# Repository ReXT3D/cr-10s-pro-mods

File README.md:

# Creality CR-10S Pro hardware mods

### CR-10S Pro Custom Transfer Board

Customized [transfer board](Transfer_Board/) to allow maximum installation flexibility when using Duet3D control boards.  Note that this modified version **is NOT** compatible with [ribbon cable breakdown board (pt)](../RibbonCable_MB_BreakdownBoard_pt/), since several ribbon cable conductors have been relocated or re-purposed in order to separate all the signal and power lines.

ReXT3D fork changes v1.0 (April 2021):

- Removed the LED connector to free-up three ribbon cable conductors.  This allows fully independent signal routing and eliminates all shared grounds and power.
- Relocated connectors for slightly better clearances.
- Added a Z_MIN connector that shares wiring with the BL_TOUCH connector.  This allows use of the stock capacitive probe, or similar capacitive or inductive probes without a need for re-pinning.
- Widened the MOTOR and HEAT traces and doubled to both layers for improved current carrying capacity.
- Slightly widened all other traces.
- Relocated TH signal wires to the edge of the ribbon cable, away from “noisy” PWM signals such as heater or fans.

ReXT3D fork changes v1.1 (May 2021):

The original board design had an error in spacing of the two mounting post holes - they were almost a millimeter to close and would not allow the board to be mounted in the printer without filing or grinding one of the holes.  The ribbon cable connector was also incorrectly offset and would not allow the black metal cover to be installed without cutting an opening in it.  Unfortunately I found all of this out **<u>after</u>** I spent money on fabricating the boards and expensive expedited shipping.  Very disappointing, but my bad for not checking the dimensions first.  While correcting these issues, I made additional significant changes for v1.1.

  - Corrected the mounting post hole spacing error.
  - Increased the mounting post pad diameter.
  - Repositioned the ribbon cable connector to allow adequate cover clearance.
  - Increased board width to match the standard 57.5 mm width of the ribbon cable connector.
  - Corrected the ribbon cable connector footprint to include holes that allow mounting to the PCB.
  - Reduced minimum copper clearances in-line with OSHPark requirements, allowing for wider stepper motor traces.
  - Re-routed and widened all other traces once again.

#### Wiring example for Duet 3 Mini 5+

The following table provides complete wiring reference for Duet 3 Mini 5+ installation in the CR-10S Pro.  This includes all of the ribbon cable signals routed through the transfer board as well as all other printer interfaces.  This has been verified and fully function tested.

#### Ready made board

I ordered version 1.1 boards from JLCPCB as opposed to OSHPark to take advantage of their quick turnaround time and they did not disappoint - I received the finished boards in five days.  The following photos  show the top and bottom of the finished board next to the Creality OEM board, as well as the finished board installed in my printer.  Note that the installation photo is visually misleading and there is plenty of clearance between the board, the wiring and the lead screw.

*I have several bare PCBs on-hand that I would be willing to part with.  Contact me if interested.*

#### Firmware configuration

I only run Klipper firmware, even on the Duet boards.  My Klipper configuration is located at [[DGUS-reloaded-Klipper-config]](https://github.com/ReXT3D/DGUS-reloaded-Klipper-config/tree/personal-duet3mini5+).

The Creality DGUS touch screen flashed with Desuuuu's slick [DGUS-reloaded-Klipper](https://github.com/Desuuuu/DGUS-reloaded-Klipper) interface now works and has been fully tested with Desuuuu's [Klipper](https://github.com/Desuuuu/klipper) branch as of his May 26, 2021 commits.  Many thanks to Desuuuu for graciously implementing the changes required to allow fully configurable serial comms with Klipper's ATSAMD code.

### CR-10S Pro Duet 3 Mini 5+ Mounting Bracket

I designed a custom mounting bracket for the Duet 3 Mini 5+ control board.  The bracket picks-up on the existing CR-10S Pro enclosure mounting points, uses metal standoffs to avoid direct plastic contacts with a potentially hot PCB, and includes mounting for the stock blower fan with a fence that routes air over the bottom side of the PCB to correctly cool the TMC2209 stepper drivers.  More details are available on Thingiverse: [CR-10S Pro Duet 3 Mini 5+ Adapter Bracket](https://www.thingiverse.com/thing:4841999)

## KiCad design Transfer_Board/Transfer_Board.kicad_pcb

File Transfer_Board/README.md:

# CR-10S Pro Custom Transfer Board
Customized [transfer board](Transfer_Board/) to allow maximum installation flexibility when using Duet3D control boards.  Note that this modified version **is NOT** compatible with [ribbon cable breakdown board (pt)](../RibbonCable_MB_BreakdownBoard_pt/), since several ribbon cable conductors have been relocated or re-purposed in order to separate all the signal and power lines.

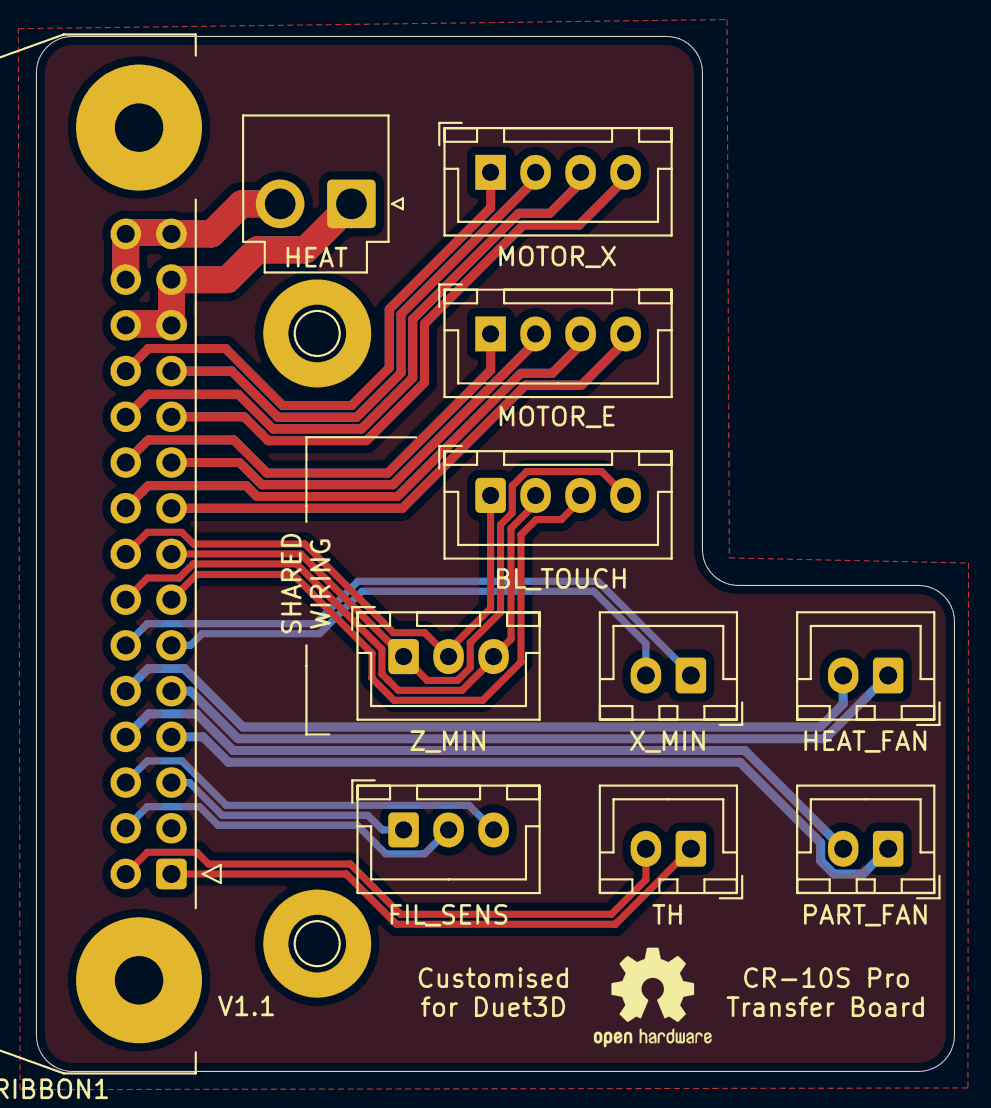
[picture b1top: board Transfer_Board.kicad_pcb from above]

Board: 2 copper layers, 51.0 x 57.5 mm, 11 parts (0 on the bottom side), 25 nets.

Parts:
BL_TOUCH: Conn_01x04; JST_XH_B4B-XH-A_1x04_P2.50mm_Vertical
FIL_SENS: Conn_01x03; JST_XH_B3B-XH-A_1x03_P2.50mm_Vertical
HEAT: Conn_01x02; JST_VH_B2P-VH-B_1x02_P3.96mm_Vertical
HEAT_FAN: Conn_01x02; JST_XH_B2B-XH-A_1x02_P2.50mm_Vertical
MOTOR_E: Conn_01x04; JST_XH_B4B-XH-A_1x04_P2.50mm_Vertical
MOTOR_X: Conn_01x04; JST_XH_B4B-XH-A_1x04_P2.50mm_Vertical
PART_FAN: Conn_01x02; JST_XH_B2B-XH-A_1x02_P2.50mm_Vertical
RIBBON1: Conn_02x15_Odd_Even; IDC-Header_2x15-1MP_P2.54mm_Latch_Horizontal
TH: Conn_01x02; JST_XH_B2B-XH-A_1x02_P2.50mm_Vertical
X_MIN: Conn_01x02; JST_XH_B2B-XH-A_1x02_P2.50mm_Vertical
Z_MIN: Conn_01x03; JST_XH_B3B-XH-A_1x03_P2.50mm_Vertical

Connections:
/+5V: BL_TOUCH.2, RIBBON1.14, Z_MIN.3
/CTRL: BL_TOUCH.3, RIBBON1.13
/GND: BL_TOUCH.1, RIBBON1.16, Z_MIN.2
/SIG: BL_TOUCH.4, RIBBON1.15, Z_MIN.1
unnamed: FIL_SENS.1, RIBBON1.5
unnamed: FIL_SENS.2, RIBBON1.4
unnamed: FIL_SENS.3, RIBBON1.6
unnamed: HEAT.1, RIBBON1.25, RIBBON1.26, RIBBON1.27
unnamed: HEAT.2, RIBBON1.28, RIBBON1.29, RIBBON1.30
unnamed: HEAT_FAN.1, RIBBON1.9
unnamed: HEAT_FAN.2, RIBBON1.10
unnamed: MOTOR_E.1, RIBBON1.20
unnamed: MOTOR_E.2, RIBBON1.19
unnamed: MOTOR_E.3, RIBBON1.18
unnamed: MOTOR_E.4, RIBBON1.17
unnamed: MOTOR_X.1, RIBBON1.24
unnamed: MOTOR_X.2, RIBBON1.23
unnamed: MOTOR_X.3, RIBBON1.22
unnamed: MOTOR_X.4, RIBBON1.21
unnamed: PART_FAN.1, RIBBON1.7
unnamed: PART_FAN.2, RIBBON1.8
unnamed: RIBBON1.1, TH.1
unnamed: RIBBON1.2, TH.2
unnamed: RIBBON1.11, X_MIN.2
unnamed: RIBBON1.12, X_MIN.1

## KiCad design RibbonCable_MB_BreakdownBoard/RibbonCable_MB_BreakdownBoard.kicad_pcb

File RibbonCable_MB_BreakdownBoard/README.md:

# Ribbon cable breakdown board
It is fully compatible with [original transfer board](https://www.aliexpress.com/item/33040303019.html), helps with wiring with non-original motherboards.

FYI, it you just want the gerber files go to 
https://github.com/SkullKill/cr-10s-pro-mods/releases

changes from fork
- Beefed up trace width where possible. 
- Heater PCB trace has trace on both Front and Back.
- Heater connector changed to  a more standard 5.08mm screw terminal
- and added I2C AT24C256 EEPROM

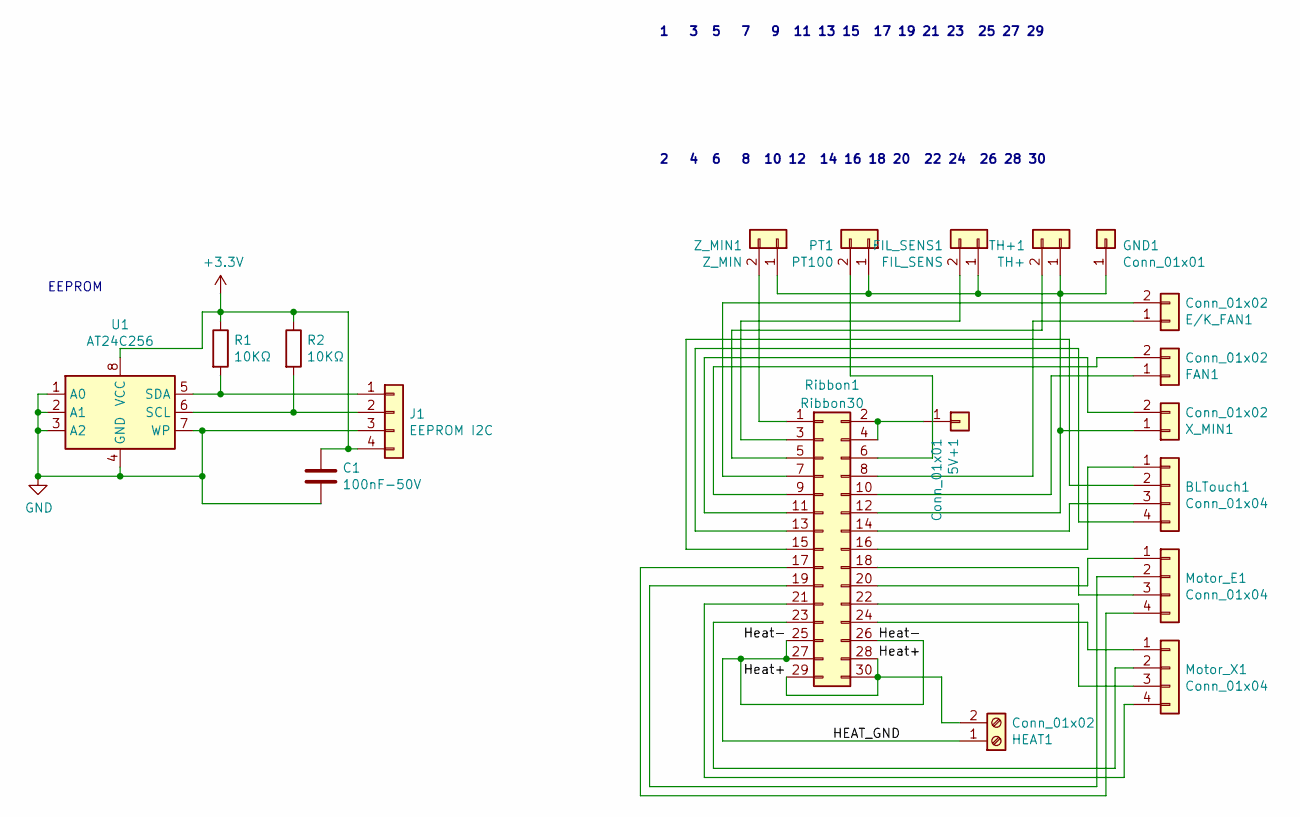
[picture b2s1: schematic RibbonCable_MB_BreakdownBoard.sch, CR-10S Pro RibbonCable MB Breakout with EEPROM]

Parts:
5V+1: Conn_01x01; PinHeader_1x01_P2.54mm_Vertical
BLTouch1: Conn_01x04; PinHeader_1x04_P2.54mm_Vertical
C1: 100nF-50V; C_0603_1608Metric; MPN AC0603KRX7R9BB104; LCSC C149620
E/K_FAN1: Conn_01x02; JST_XH_B2B-XH-A_1x02_P2.50mm_Vertical
FAN1: Conn_01x02; JST_XH_B2B-XH-A_1x02_P2.50mm_Vertical
FIL_SENS1: FIL_SENS; JST_XH_B2B-XH-A_1x02_P2.50mm_Vertical
GND1: Conn_01x01; PinHeader_1x01_P2.54mm_Vertical
HEAT1: Conn_01x02; TerminalBlock_bornier-2_P5.08mm; MPN KF128-2.54-4P
J1: EEPROM I2C; PinHeader_1x04_P2.54mm_Vertical
Motor_E1: Conn_01x04; JST_XH_B4B-XH-A_1x04_P2.50mm_Vertical
Motor_X1: Conn_01x04; JST_XH_B4B-XH-A_1x04_P2.50mm_Vertical
PT1: PT100; JST_XH_B2B-XH-A_1x02_P2.50mm_Vertical
R1, R2: 10KΩ; R_0603_1608Metric; MPN RC0603FR-0710KL; LCSC C98220
Ribbon1: Ribbon30; IDC-Header_2x15_P2.54mm_Vertical; MPN C79824; LCSC C79824
TH+1: TH+; JST_XH_B2B-XH-A_1x02_P2.50mm_Vertical
U1: AT24C256; SOIC-8_3.9x4.9mm_P1.27mm; MPN AT24C256C-SSHL-T; LCSC C6482
X_MIN1: Conn_01x02; JST_XH_B2B-XH-A_1x02_P2.50mm_Vertical
Z_MIN1: Z_MIN; JST_XH_B2B-XH-A_1x02_P2.50mm_Vertical

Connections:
+3V3: C1.1, J1.4, R1.1, R2.1, U1.8 (VCC)
/HEAT_GND: HEAT1.1, Ribbon1.25, Ribbon1.26, Ribbon1.27
/Heat+: HEAT1.2, Ribbon1.28, Ribbon1.29, Ribbon1.30
GND: C1.2, J1.3, U1.1 (A0), U1.2 (A1), U1.3 (A2), U1.4 (GND), U1.7 (WP)
unnamed: 5V+1.1, Ribbon1.2, Ribbon1.4
unnamed: BLTouch1.1, Ribbon1.16
unnamed: BLTouch1.2, Ribbon1.15
unnamed: BLTouch1.3, Ribbon1.14
unnamed: BLTouch1.4, Ribbon1.13
unnamed: E/K_FAN1.1, Ribbon1.8
unnamed: E/K_FAN1.2, Ribbon1.7
unnamed: FAN1.1, Ribbon1.10
unnamed: FAN1.2, Ribbon1.9
unnamed: FIL_SENS1.1, GND1.1, PT1.1, Ribbon1.12, TH+1.1, X_MIN1.1, Z_MIN1.1
unnamed: FIL_SENS1.2, Ribbon1.3
unnamed: J1.1, R1.2, U1.5 (SDA)
unnamed: J1.2, R2.2, U1.6 (SCL)
unnamed: Motor_E1.1, Ribbon1.20
unnamed: Motor_E1.2, Ribbon1.19
unnamed: Motor_E1.3, Ribbon1.18
unnamed: Motor_E1.4, Ribbon1.17
unnamed: Motor_X1.1, Ribbon1.24
unnamed: Motor_X1.2, Ribbon1.23
unnamed: Motor_X1.3, Ribbon1.22
unnamed: Motor_X1.4, Ribbon1.21
unnamed: PT1.2, Ribbon1.6
unnamed: Ribbon1.1, Z_MIN1.2
unnamed: Ribbon1.5, TH+1.2
unnamed: Ribbon1.11, X_MIN1.2

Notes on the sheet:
2 4 6 8 10 12 14 16 18 20 22 24 26 28 30
1 3 5 7 9 11 13 15 17 19 21 23 25 27 29
EEPROM

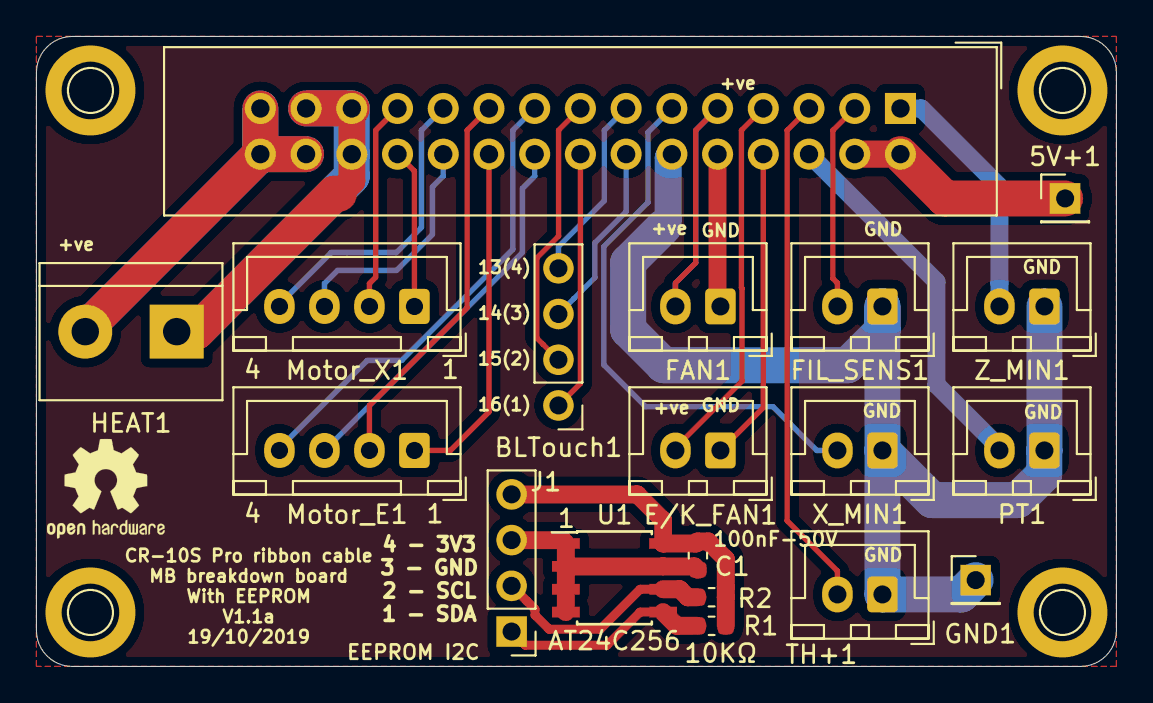
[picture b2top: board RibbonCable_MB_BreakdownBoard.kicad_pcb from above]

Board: 2 copper layers, 60.0 x 35.0 mm, 19 parts (0 on the bottom side), 29 nets.

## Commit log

2019-10-14 Create test
2019-10-14 beefed up trace and added EEPROM
    Beefed up trace width where possible.
    Heater PCB trace has trace on both Front and Back.
    Heater connector changed to a more standard 5.08mm screw terminal
    and added I2C AT24C256 EEPROM
2019-11-19 updated silkscreen to have more info
2021-04-21 Modified to allow use of Duet3D control boards
    Modified the Transfer Board to allow use of Duet3D control boards. The following changes have been made: relocated connectors, removed LED connector to free-up pins for fully independent signal routi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
2021-04-21 Updated description and images
    Updated description to align with ReXT3D changes. Updated board images to their OSHPark renditions.
2021-04-21 Fix README.md typo
2021-04-21 More updates to README.md
2021-05-02 Revised board to v1.1
    Corrected original board geometry errors and incorporated additional improvements.
2021-05-02 Bottom silkscreen correction
    Corrected TH pin assignment on bottom silkscreen. Small tweaks to README.md.
2021-05-02 Added note about unfinished WIP
2021-05-02 Rationalization of connector pinouts and ribbon cable assignments
2021-05-22 Finalized wiring table & included finished board photos
2021-05-22 Enlarged images and included reference to Klipper config
2021-05-22 Updated README.md with note about availability of bare PCBs
2021-06-09 Updated README.md to indicate fully functional DGUS touch screen
